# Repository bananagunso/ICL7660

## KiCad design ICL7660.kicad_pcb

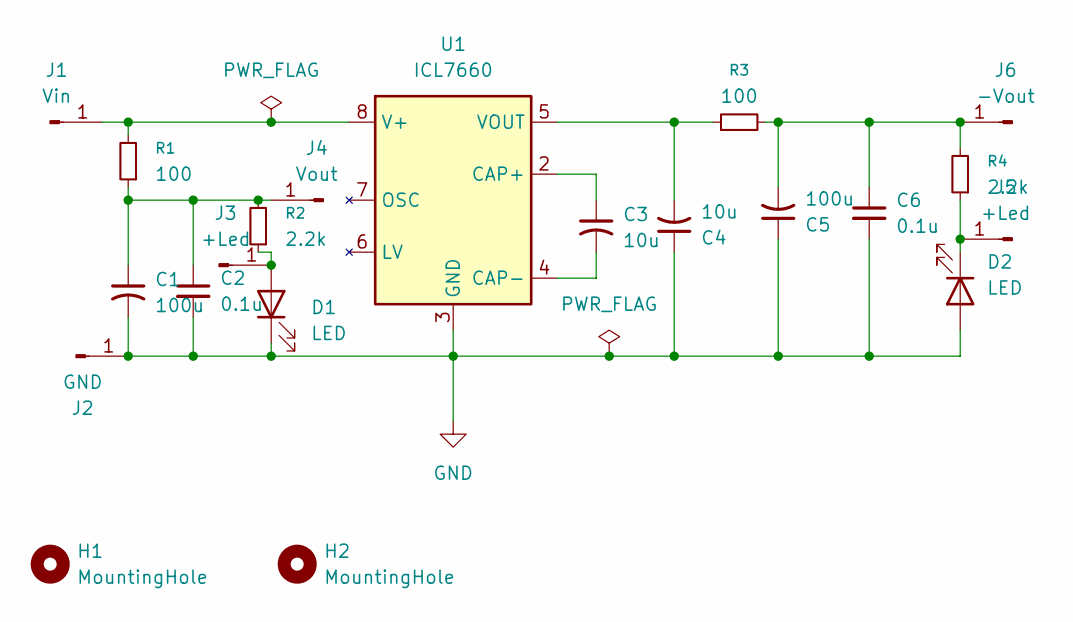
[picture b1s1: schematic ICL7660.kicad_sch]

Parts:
C1, C5: 100u; CP_Radial_D10.0mm_P2.50mm
C2, C6: 0.1u; C_Disc_D5.0mm_W2.5mm_P2.50mm
C3, C4: 10u; CP_Radial_D6.3mm_P2.50mm
D1, D2: LED
H1, H2: MountingHole; MountingHole_3.2mm_M3
J1: Vin; PinHeader_1x01_P2.54mm_Vertical
J2: GND; PinHeader_1x01_P2.54mm_Vertical
J3, J5: +Led; PinHeader_1x01_P2.54mm_Vertical
J4: Vout; PinHeader_1x01_P2.54mm_Vertical
J6: -Vout; PinHeader_1x01_P2.54mm_Vertical
R1, R3: 100; R_Axial_DIN0204_L3.6mm_D1.6mm_P2.54mm_Vertical
R2, R4: 2.2k; R_Axial_DIN0204_L3.6mm_D1.6mm_P2.54mm_Vertical
U1: ICL7660; CERDIP-8_W7.62mm_SideBrazed_Socket

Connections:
GND: C1.2, C2.2, C4.1, C5.1, C6.2, D1.1 (K), D2.2 (A), J2.1, U1.3 (GND)
unnamed: D1.2 (A), J3.1, R2.1
unnamed: D2.1 (K), J5.1, R4.1
unnamed: J1.1, R1.2, U1.8 (V+)
unnamed: C1.1, C2.1, J4.1, R1.1, R2.2
unnamed: C5.2, C6.1, J6.1, R3.2, R4.2
unnamed: C3.1, U1.2 (CAP+)
unnamed: C3.2, U1.4 (CAP-)
unnamed: C4.2, R3.1, U1.5 (VOUT)

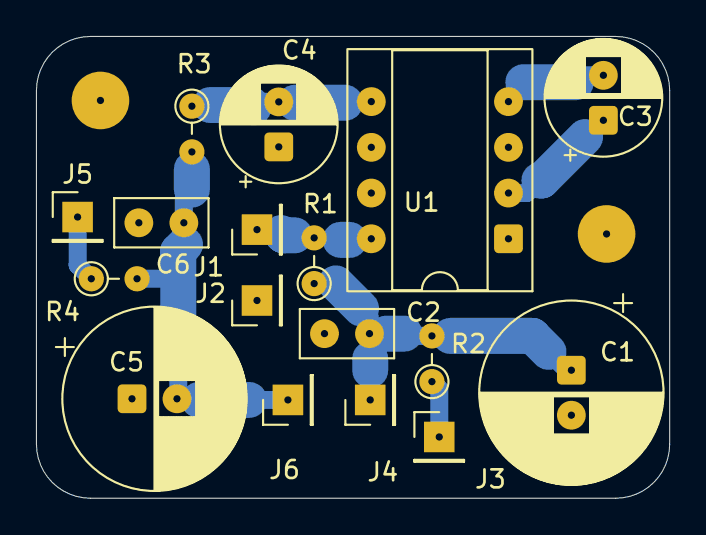
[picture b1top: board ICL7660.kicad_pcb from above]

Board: 2 copper layers, 35.2 x 25.7 mm, 19 parts (0 on the bottom side), 9 nets.

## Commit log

2026-02-28 SなしのICL7660でノイズを除去した両電源
2026-03-01 配置を修正
2026-03-01 LED用の抵抗を追加
2026-03-01 ドリル穴のサイズを修正
